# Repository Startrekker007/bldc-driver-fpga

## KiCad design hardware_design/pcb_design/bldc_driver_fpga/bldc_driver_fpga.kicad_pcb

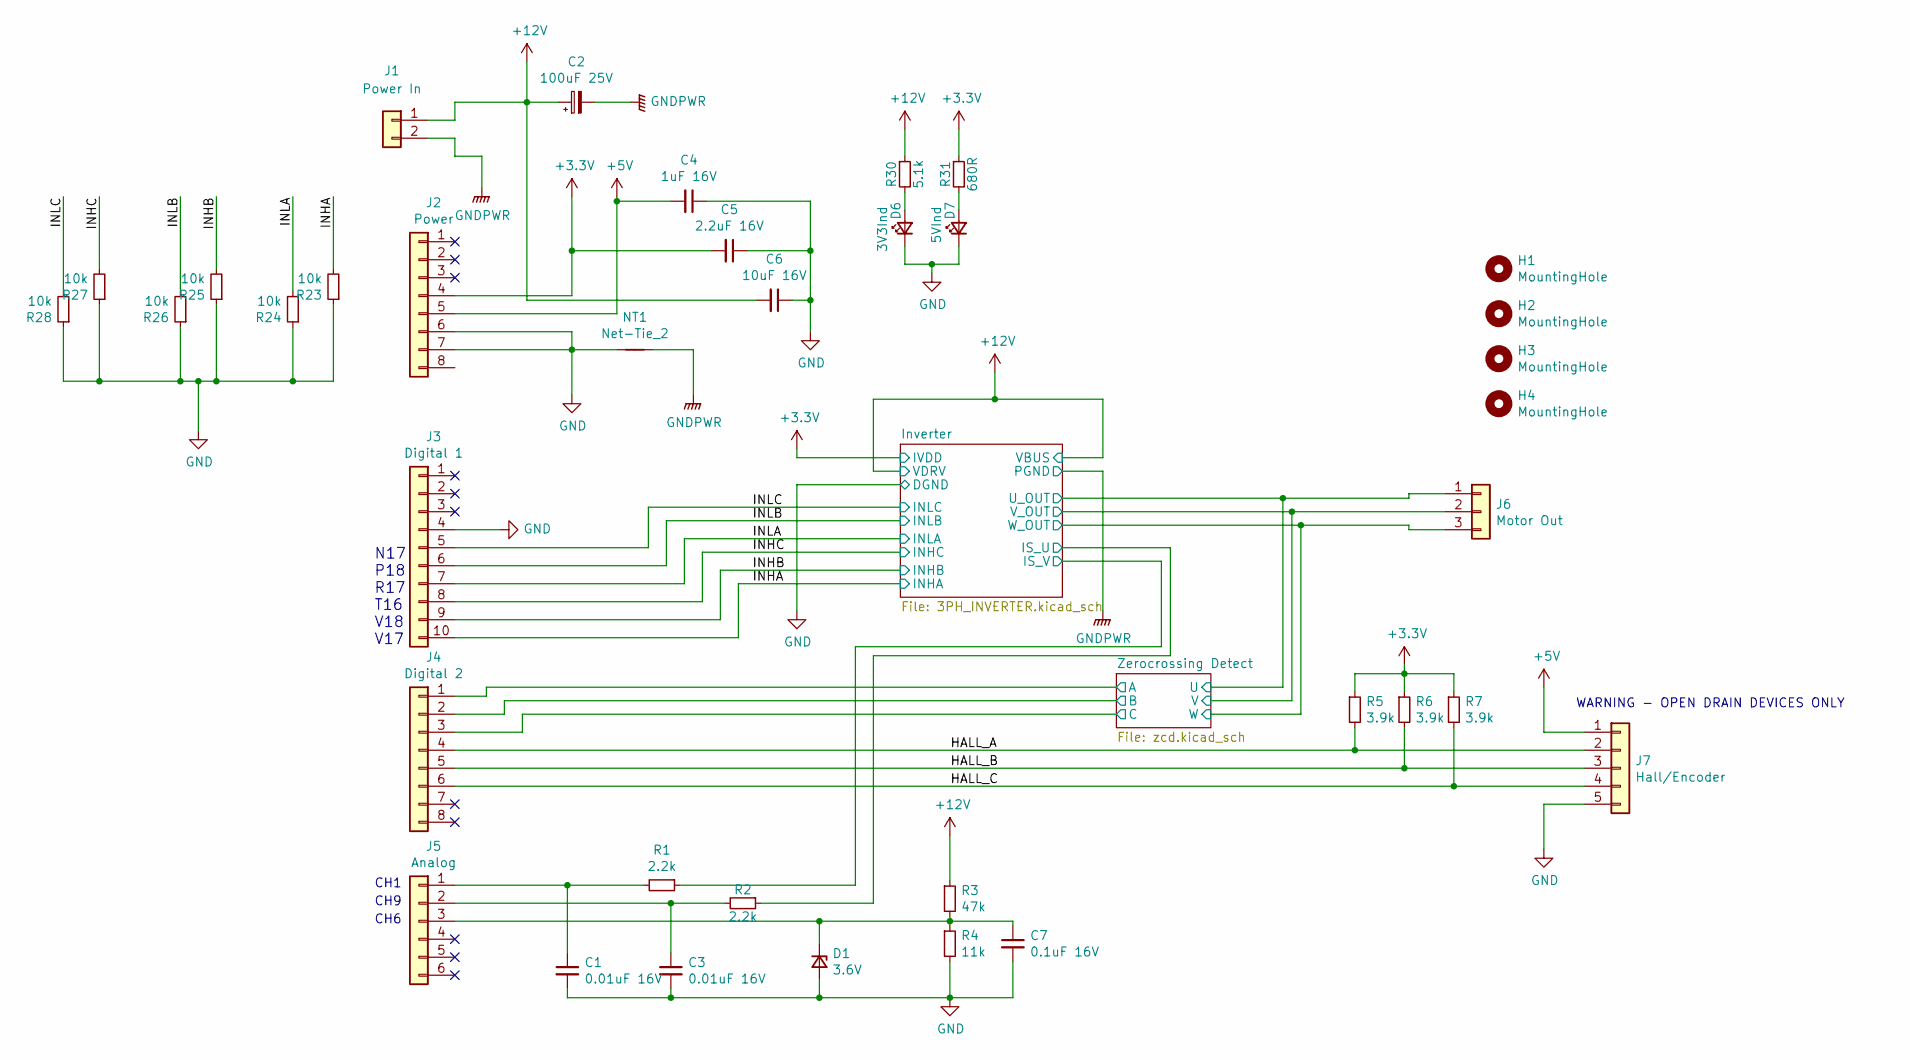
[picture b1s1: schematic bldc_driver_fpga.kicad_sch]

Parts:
C1, C3: 0.01uF 16V; C_0603_1608Metric_Pad1.08x0.95mm_HandSolder
C2: 100uF 25V; CP_Elec_6.3x5.7; MPN VZS101M1ETR-0606
C4: 1uF 16V; C_0603_1608Metric_Pad1.08x0.95mm_HandSolder
C5: 2.2uF 16V; C_0603_1608Metric_Pad1.08x0.95mm_HandSolder
C6: 10uF 16V; C_0603_1608Metric_Pad1.08x0.95mm_HandSolder
C7: 0.1uF 16V; C_0603_1608Metric_Pad1.08x0.95mm_HandSolder
D1: 3.6V; D_SOD-523; MPN MM5Z4685T1G
D6: 3V3Ind; LED_0603_1608Metric_Pad1.05x0.95mm_HandSolder
D7: 5VInd; LED_0603_1608Metric_Pad1.05x0.95mm_HandSolder
H1, H2, H3, H4: MountingHole; MountingHole_3.2mm_M3
J1: Power In; JST_PH_B2B-PH-K_1x02_P2.00mm_Vertical
J2: Power; PinHeader_1x08_P2.54mm_Vertical
J3: Digital 1; PinHeader_1x10_P2.54mm_Vertical
J4: Digital 2; PinHeader_1x08_P2.54mm_Vertical
J5: Analog; PinHeader_1x06_P2.54mm_Vertical
J6: Motor Out; JST_PH_B3B-PH-K_1x03_P2.00mm_Vertical; MPN 105430-1103
J7: Hall/Encoder; JST_PH_B5B-PH-K_1x05_P2.00mm_Vertical
NT1: Net-Tie_2; NetTie-2_SMD_Pad2.0mm
R1, R2: 2.2k; R_0603_1608Metric_Pad0.98x0.95mm_HandSolder
R3: 47k; R_0603_1608Metric_Pad0.98x0.95mm_HandSolder
R4: 11k; R_0603_1608Metric_Pad0.98x0.95mm_HandSolder
R5, R6, R7: 3.9k; R_0603_1608Metric_Pad0.98x0.95mm_HandSolder
R23, R24, R25, R26, R27, R28: 10k; R_0603_1608Metric_Pad0.98x0.95mm_HandSolder
R30: 5.1k; R_0603_1608Metric_Pad0.98x0.95mm_HandSolder
R31: 680R; R_0603_1608Metric_Pad0.98x0.95mm_HandSolder

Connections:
+3V3: C5.2, J2.4, R5.1, R6.1, R7.1, R31.1; also elsewhere on the board
+5V: C4.2, J2.5, J7.1
+12V: C2.1, C6.2, J1.1, R3.1, R30.1; also elsewhere on the board
/HALL_A: J4.4, J7.2, R5.2
/HALL_B: J4.5, J7.3, R6.2
/HALL_C: J4.6, J7.4, R7.2
/INHA: J3.10, R23.2; also elsewhere on the board
/INHB: J3.9, R25.2; also elsewhere on the board
/INHC: J3.8, R27.2; also elsewhere on the board
/INLA: J3.7, R24.2; also elsewhere on the board
/INLB: J3.6, R26.2; also elsewhere on the board
/INLC: J3.5, R28.2; also elsewhere on the board
/Inverter/IS_U: R2.1; also elsewhere on the board
/Inverter/IS_V: R1.1; also elsewhere on the board
/Inverter/U_OUT: J6.1; also elsewhere on the board
/Inverter/V_OUT: J6.2; also elsewhere on the board
/Inverter/W_OUT: J6.3; also elsewhere on the board
/Zerocrossing Detect/A: J4.1; also elsewhere on the board
/Zerocrossing Detect/B: J4.2; also elsewhere on the board
/Zerocrossing Detect/C: J4.3; also elsewhere on the board
GND: C1.2, C3.2, C4.1, C5.1, C6.1, C7.2, D1.2 (A), D6.1 (K), D7.1 (K), J2.6, J2.7, J3.4, J7.5, NT1.1, R4.2, R23.1, R24.1, R25.1, R26.1, R27.1, R28.1; also elsewhere on the board
GNDPWR: C2.2, J1.2, NT1.2; also elsewhere on the board
unnamed: C1.1, J5.1, R1.2
unnamed: C3.1, J5.2, R2.2
unnamed: C7.1, D1.1 (K), J5.3, R3.2, R4.1
unnamed: D6.2 (A), R30.2
unnamed: D7.2 (A), R31.2

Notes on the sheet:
WARNING - OPEN DRAIN DEVICES ONLY
N17 P18 R17 T16 V18 V17
CH6
CH1
CH9

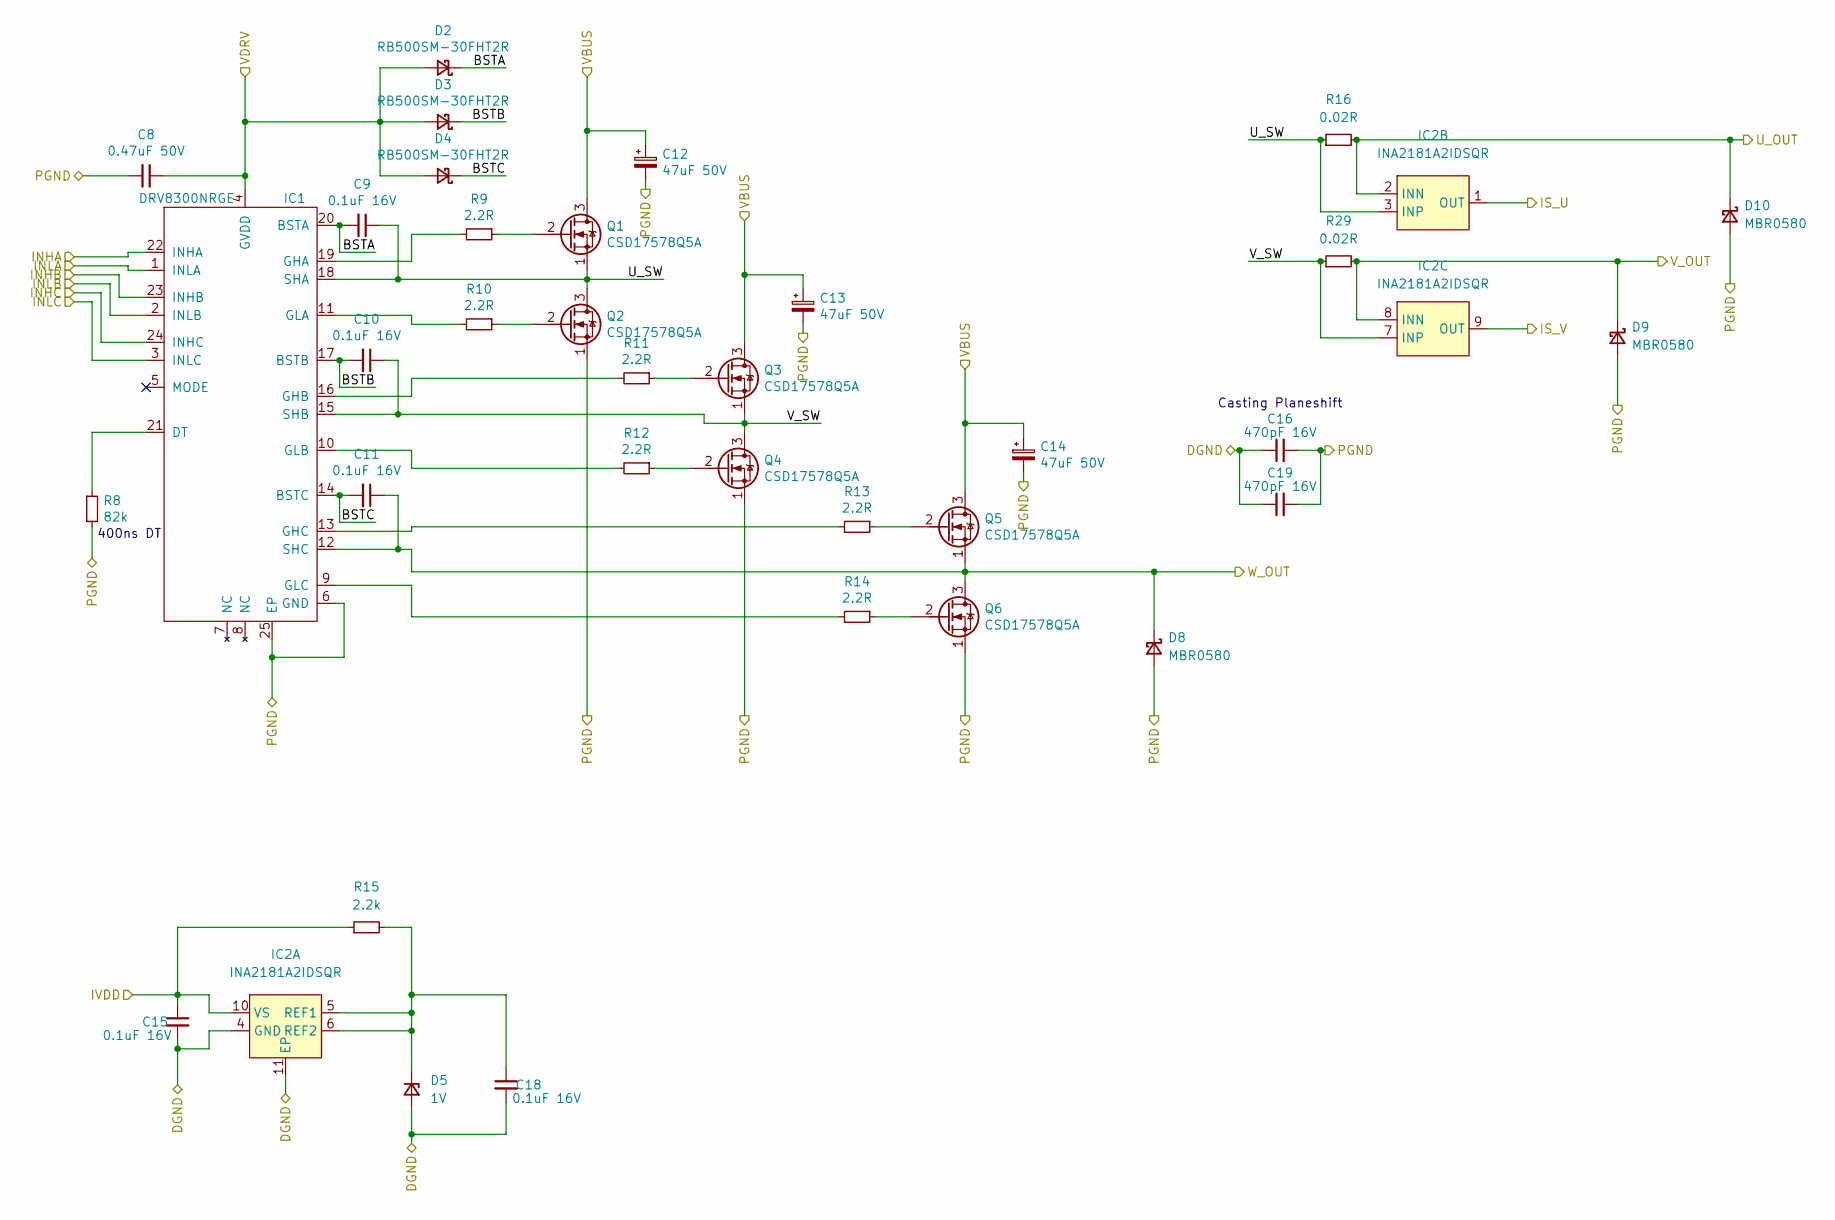
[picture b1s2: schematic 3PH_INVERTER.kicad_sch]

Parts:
C8: 0.47uF 50V; C_0603_1608Metric_Pad1.08x0.95mm_HandSolder
C9, C10, C11, C15, C18: 0.1uF 16V; C_0603_1608Metric_Pad1.08x0.95mm_HandSolder
C12, C13, C14: 47uF 50V; CP_Elec_6.3x5.7; MPN 865080443007
C16, C19: 470pF 16V; C_0603_1608Metric_Pad1.08x0.95mm_HandSolder
D2, D3, D4: RB500SM-30FHT2R; D_SOD-523
D5: 1V; SOT-23
D8, D9, D10: MBR0580; D_SOD-123F
IC1: DRV8300NRGE; VQFN-24-1EP_4x4mm_P0.5mm_EP2.45x2.45mm_ThermalViasBig
IC2: INA2181A2IDSQR; WSON-10-1EP_2.0x2.0mm_P0.4mm_EP0.9x1.5mm
Q1, Q3, Q5: CSD17578Q5A; TDSON-8-1_HandSolderingVias_SGD
Q2, Q4, Q6: CSD17578Q5A; TDSON-8-1_HandSoldering_SGD
R8: 82k; R_0603_1608Metric_Pad0.98x0.95mm_HandSolder
R9, R10, R11, R12, R13, R14: 2.2R; R_0603_1608Metric_Pad0.98x0.95mm_HandSolder
R15: 2.2k; R_0603_1608Metric_Pad0.98x0.95mm_HandSolder
R16, R29: 0.02R; R_1206_3216Metric_Pad1.30x1.75mm_HandSolder

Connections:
+3V3: C15.1, IC2.10 (VS), R15.1; also elsewhere on the board
+12V: C8.1, C12.1, C13.1, C14.1, D2.2 (A), D3.2 (A), D4.2 (A), IC1.4 (GVDD), Q1.3 (D), Q3.3 (D), Q5.3 (D); also elsewhere on the board
/INHA: IC1.22 (INHA); also elsewhere on the board
/INHB: IC1.23 (INHB); also elsewhere on the board
/INHC: IC1.24 (INHC); also elsewhere on the board
/INLA: IC1.1 (INLA); also elsewhere on the board
/INLB: IC1.2 (INLB); also elsewhere on the board
/INLC: IC1.3 (INLC); also elsewhere on the board
/Inverter/BSTA: C9.2, D2.1 (K), IC1.20 (BSTA)
/Inverter/BSTB: C10.2, D3.1 (K), IC1.17 (BSTB)
/Inverter/BSTC: C11.2, D4.1 (K), IC1.14 (BSTC)
/Inverter/IS_U: IC2.1 (OUT); also elsewhere on the board
/Inverter/IS_V: IC2.9 (OUT); also elsewhere on the board
/Inverter/U_OUT: D10.1 (K), IC2.2 (INN), R16.2; also elsewhere on the board
/Inverter/U_SW: C9.1, IC1.18 (SHA), IC2.3 (INP), Q1.1 (S), Q2.3 (D), R16.1
/Inverter/V_OUT: D9.1 (K), IC2.8 (INN), R29.2; also elsewhere on the board
/Inverter/V_SW: C10.1, IC1.15 (SHB), IC2.7 (INP), Q3.1 (S), Q4.3 (D), R29.1
/Inverter/W_OUT: C11.1, D8.1 (K), IC1.12 (SHC), Q5.1 (S), Q6.3 (D); also elsewhere on the board
GND: C15.2, C16.1, C18.2, C19.1, D5.2 (A), IC2.4 (GND), IC2.11 (EP); also elsewhere on the board
GNDPWR: C8.2, C12.2, C13.2, C14.2, C16.2, C19.2, D8.2 (A), D9.2 (A), D10.2 (A), IC1.6 (GND), IC1.25 (EP), Q2.1 (S), Q4.1 (S), Q6.1 (S), R8.2; also elsewhere on the board
unnamed: C18.1, D5.1 (K), IC2.5 (REF1), IC2.6 (REF2), R15.2
unnamed: IC1.9 (GLC), R14.2
unnamed: IC1.10 (GLB), R12.2
unnamed: IC1.11 (GLA), R10.2
unnamed: IC1.13 (GHC), R13.2
unnamed: IC1.16 (GHB), R11.2
unnamed: IC1.19 (GHA), R9.2
unnamed: IC1.21 (DT), R8.1
unnamed: Q1.2 (G), R9.1
unnamed: Q2.2 (G), R10.1
unnamed: Q3.2 (G), R11.1
unnamed: Q4.2 (G), R12.1
unnamed: Q5.2 (G), R13.1
unnamed: Q6.2 (G), R14.1

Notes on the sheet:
Casting Planeshift
400ns DT

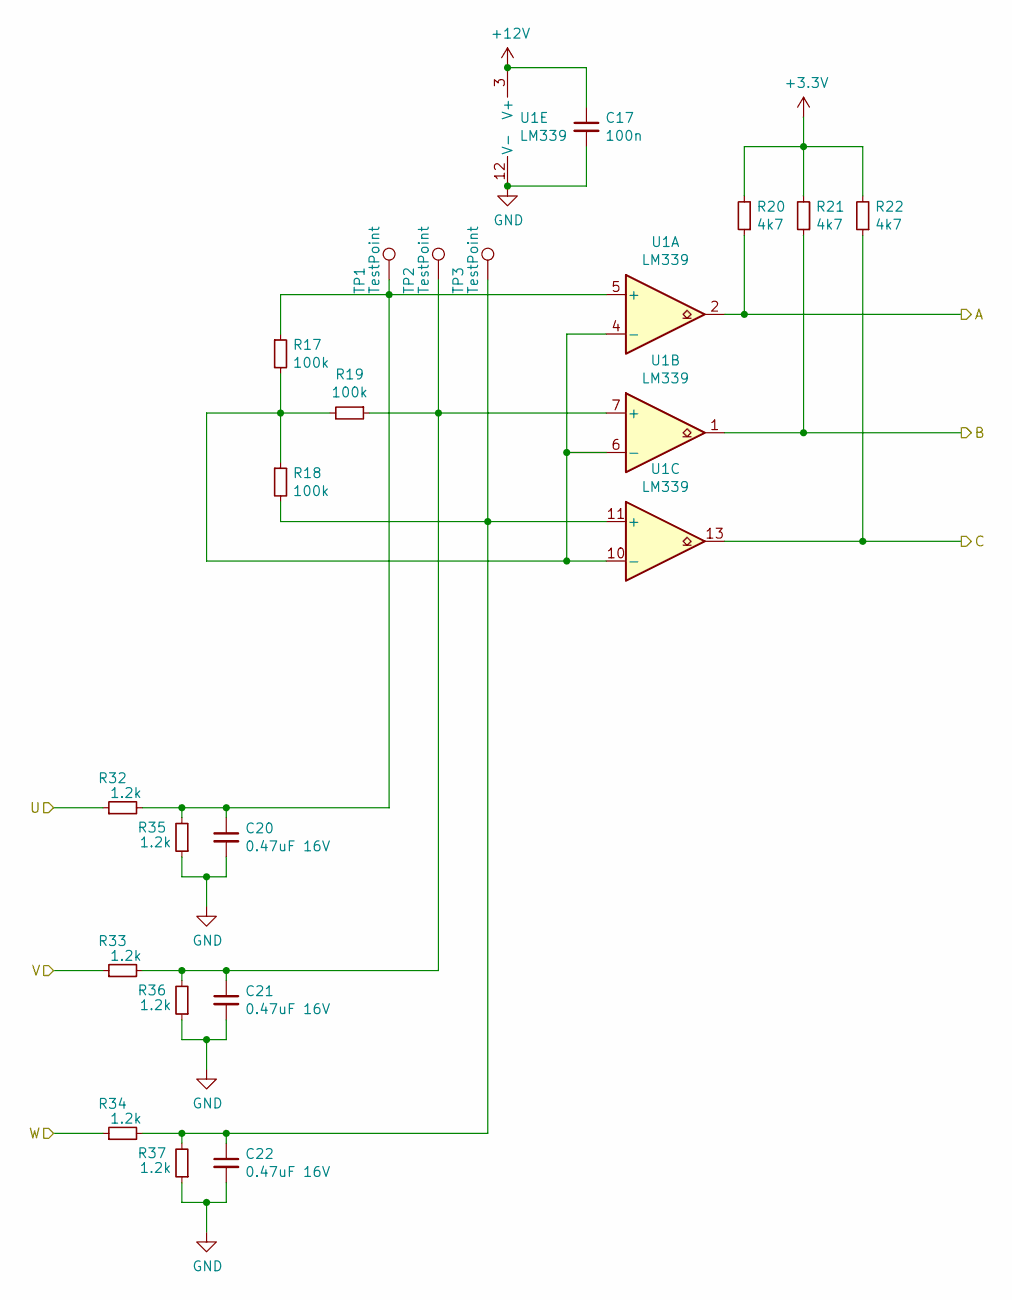
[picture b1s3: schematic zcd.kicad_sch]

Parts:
C17: 100n; C_0603_1608Metric_Pad1.08x0.95mm_HandSolder
C20, C21, C22: 0.47uF 16V; C_0603_1608Metric_Pad1.08x0.95mm_HandSolder
R17, R18, R19: 100k; R_0603_1608Metric_Pad0.98x0.95mm_HandSolder
R20, R21, R22: 4k7; R_0603_1608Metric_Pad0.98x0.95mm_HandSolder
R32, R33, R34, R35, R36, R37: 1.2k; R_0603_1608Metric_Pad0.98x0.95mm_HandSolder
TP1, TP2, TP3: TestPoint; TestPoint_Pad_1.0x1.0mm
U1: LM339; SOIC-14_3.9x8.7mm_P1.27mm

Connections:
+3V3: R20.2, R21.2, R22.2; also elsewhere on the board
+12V: C17.1, U1.3 (V+); also elsewhere on the board
/Inverter/U_OUT: R32.1; also elsewhere on the board
/Inverter/V_OUT: R33.1; also elsewhere on the board
/Inverter/W_OUT: R34.1; also elsewhere on the board
/Zerocrossing Detect/A: R20.1, U1.2; also elsewhere on the board
/Zerocrossing Detect/B: R21.1, U1.1; also elsewhere on the board
/Zerocrossing Detect/C: R22.1, U1.13; also elsewhere on the board
GND: C17.2, C20.2, C21.2, C22.2, R35.1, R36.1, R37.1, U1.12 (V-); also elsewhere on the board
unnamed: C20.1, R17.1, R32.2, R35.2, TP1.1, U1.5 (+)
unnamed: C21.1, R19.1, R33.2, R36.2, TP2.1, U1.7 (+)
unnamed: C22.1, R18.2, R34.2, R37.2, TP3.1, U1.11 (+)
unnamed: R17.2, R18.1, R19.2, U1.4 (-), U1.6 (-), U1.10 (-)

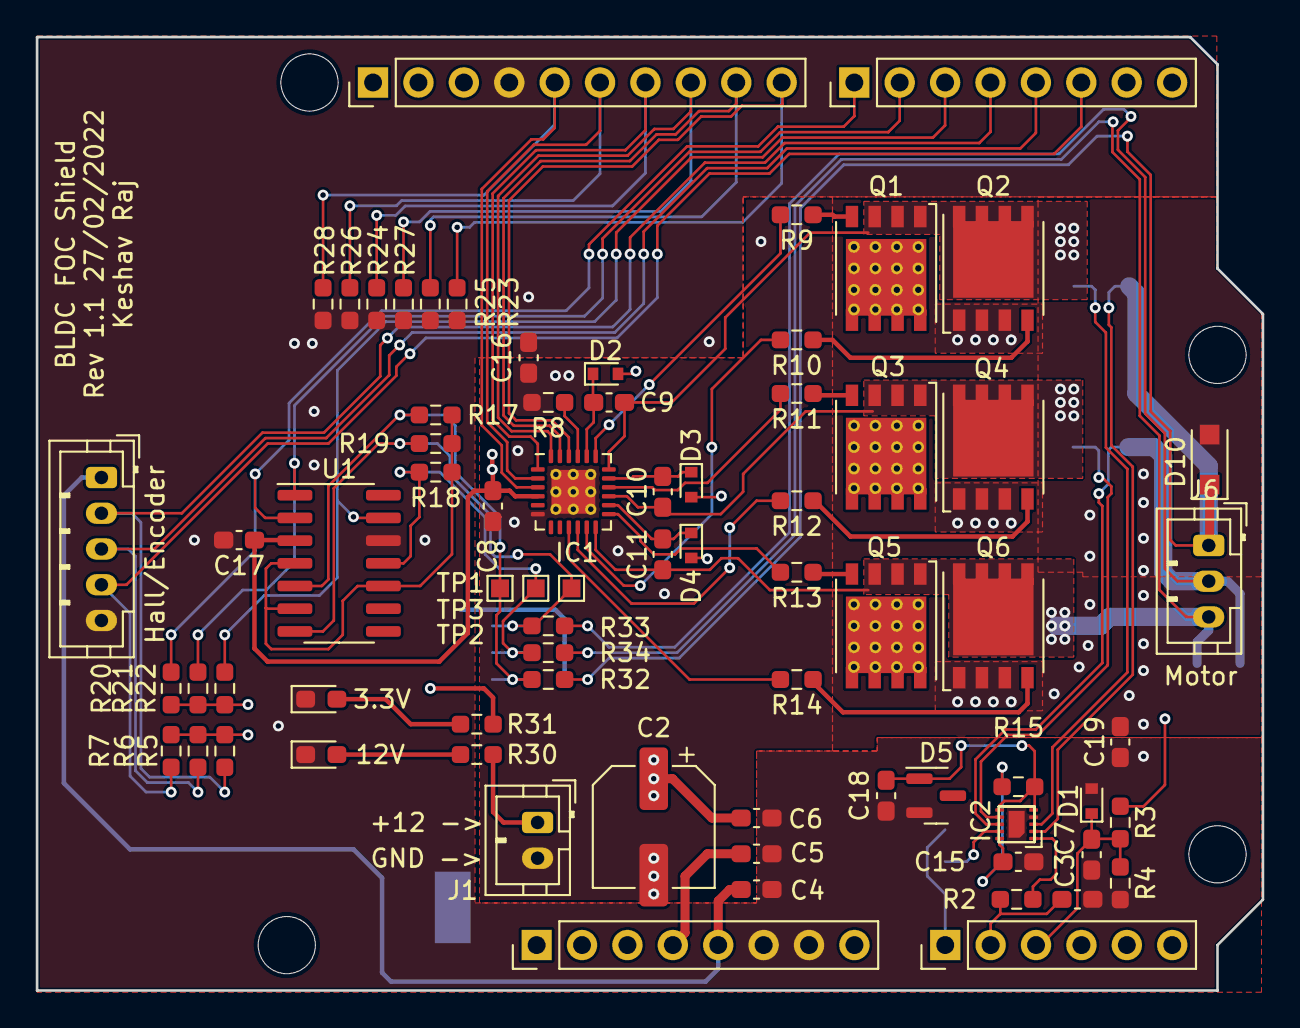
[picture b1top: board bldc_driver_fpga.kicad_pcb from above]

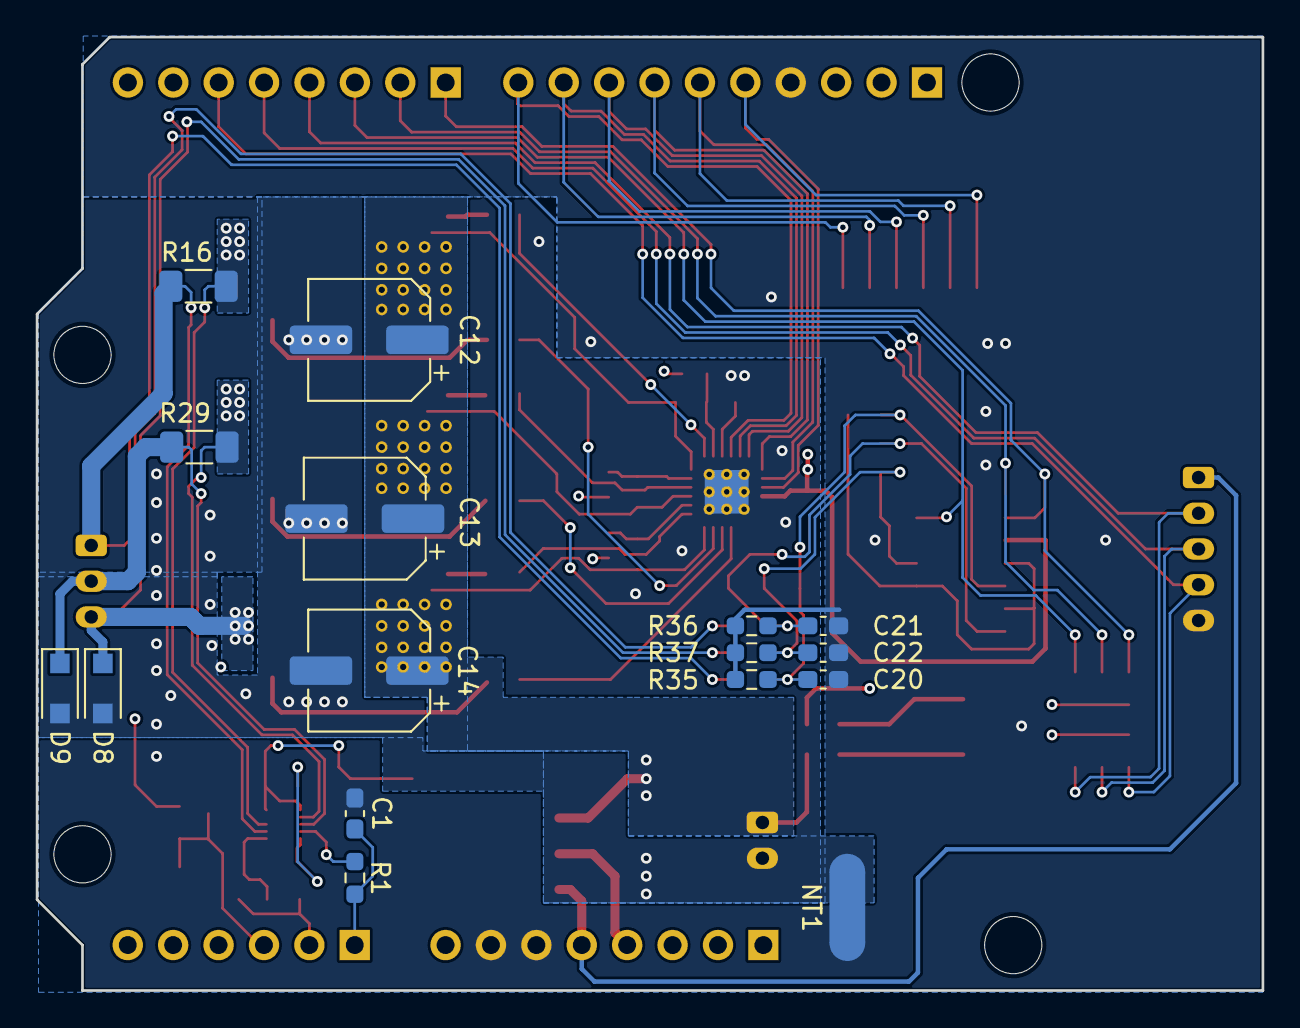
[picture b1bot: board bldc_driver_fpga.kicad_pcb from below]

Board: 4 copper layers, 68.6 x 53.3 mm, 93 parts (16 on the bottom side), 50 nets.

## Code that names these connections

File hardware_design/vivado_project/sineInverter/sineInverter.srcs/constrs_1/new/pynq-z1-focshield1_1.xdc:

set_property IOSTANDARD LVCMOS33 [get_ports INHA]
set_property IOSTANDARD LVCMOS33 [get_ports INHB]
set_property IOSTANDARD LVCMOS33 [get_ports INHC]
set_property IOSTANDARD LVCMOS33 [get_ports INLA]
set_property IOSTANDARD LVCMOS33 [get_ports INLB]
set_property IOSTANDARD LVCMOS33 [get_ports INLC]
set_property PACKAGE_PIN V17 [get_ports INHA]
set_property PACKAGE_PIN V18 [get_ports INHB]
set_property PACKAGE_PIN T16 [get_ports INHC]
set_property PACKAGE_PIN R17 [get_ports INLA]
set_property PACKAGE_PIN P18 [get_ports INLB]
set_property PACKAGE_PIN N17 [get_ports INLC]

set_property IOSTANDARD LVCMOS33 [get_ports indicator_0]
set_property PACKAGE_PIN N15 [get_ports indicator_0]

set_property PACKAGE_PIN D18 [get_ports Vaux1_0_v_n]
set_property IOSTANDARD LVCMOS33 [get_ports Vaux1_0_v_n]
set_property IOSTANDARD LVCMOS33 [get_ports Vaux1_0_v_p]
set_property IOSTANDARD LVCMOS33 [get_ports Vaux6_0_v_n]
set_property IOSTANDARD LVCMOS33 [get_ports Vaux6_0_v_p]
set_property IOSTANDARD LVCMOS33 [get_ports Vaux9_0_v_n]
set_property IOSTANDARD LVCMOS33 [get_ports Vaux9_0_v_p]
set_property IOSTANDARD LVCMOS33 [get_ports full]
set_property PACKAGE_PIN G14 [get_ports full]

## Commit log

2021-10-16 Moving project to github
2021-10-16 Constraints set, bitstream generated, block diagram tcl written.
2021-11-04 Created ADC test overlay
2022-01-06 Implemented automatic XADC channel sequencing and arranging of outpuit data into seperate data channels.
2022-02-19 Implemented inverse clarke and inverse park hardware modules. Implemented ADC trigger logic and data output identification from XADC.
2022-02-22 Tested inverter, works. Tested ADC triggering, mostly works except not sure if current is correct. Found issue with back EMF causing FPGA to crash.
2022-08-06 Implemented pure sinewave drive from programmable logic. Set up time base generator for ADC.
2022-09-04 Implemented DMA based ADC readouts. Ready to measure current waveforms!
